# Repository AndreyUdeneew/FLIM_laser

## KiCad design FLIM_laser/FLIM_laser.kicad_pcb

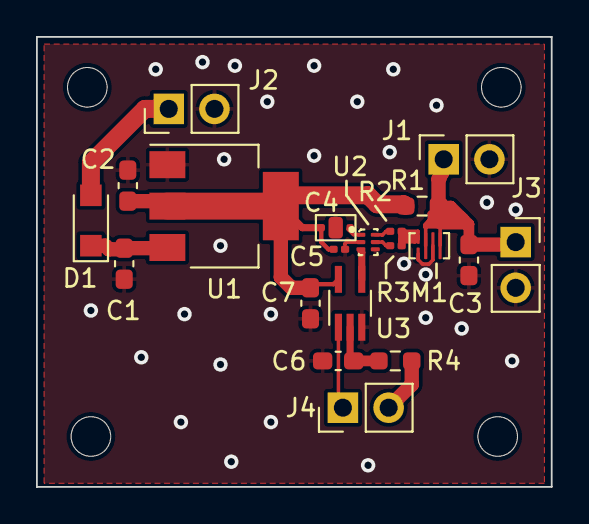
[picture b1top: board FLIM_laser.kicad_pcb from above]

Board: 2 copper layers, 28.6 x 25.0 mm, 20 parts (0 on the bottom side), 13 nets.

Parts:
C1, C2, C3, C6, C7: C; C_0603_1608Metric_Pad1.08x0.95mm_HandSolder
C4: C_Feedthrough; YFF18PW0J474M
C5: C; C_0201_0603Metric
D1: PMEG40T10ER; Nexperia_CFP3_SOD-123W
J1, J3: Conn_01x02_Male; PinSocket_1x02_P2.54mm_Vertical
J2, J4: Conn_01x02_Male; PinHeader_1x02_P2.54mm_Vertical
M1: EP2014C; EPC2014C
R1, R4: R; R_0603_1608Metric_Pad0.98x0.95mm_HandSolder
R2, R3: R; R_0201_0603Metric
U1: AMS1117-5.0; SOT-223-3_TabPin2
U2: LMG1020
U3: 74LVC1G08; SOT-353_SC-70-5_Handsoldering

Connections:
+5V: C2.1, C4.1, C5.1, C7.1, R1.1, U1.2 (VO), U3.5 (VCC)
GND: C1.2, C2.2, C3.2, C4.2, C5.2, C6.2, C7.2, J1.2, J2.2, J3.2, M1.2 (Sub), M1.4 (S), U1.1 (GND), U2.B1 (GND), U2.C2 (IN-), U3.3 (GND)
unnamed: C1.1, D1.1 (K), U1.3 (VI)
unnamed: C3.1, J1.1, J3.1, M1.3 (D), M1.5 (D), R1.2
unnamed: C6.1, R4.2, U3.2
unnamed: D1.2 (A), J2.1
unnamed: J4.1, U3.1
unnamed: J4.2, R4.1
unnamed: M1.1 (G), R2.2, R3.2
unnamed: R2.1, U2.A2 (OUTH)
unnamed: R3.1, U2.B2 (OUTL)
unnamed: C4.3, U2.A1 (VDD)
unnamed: U2.C1 (IN+), U3.4

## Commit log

2022-03-09 v0.1 files were created
2022-03-10 v0.1 library and circuit were created
2022-03-10 v0.2 correct connector was added
2022-03-10 v0.3 circuit is ready
2022-05-06 v0.4 correct symbols were added
2022-05-07 v0.5 power source was added
2022-05-07 v0.6 input shottky was added
2022-05-10 v0.7 PCB prototype was created, components were decomposed
2022-05-12 v0.8 footprints were corrected
2022-05-12 v0.9 decomposition was completed
2022-05-12 v0.91 some changes
2022-05-12 v0.92 subcompleted
2022-05-12 v0.93 subcomplected 2
2022-05-13 v0.94 something
2022-05-14 v0.95 DRC was conducted
2022-05-16 v0.96 Silk was corrected
2022-05-16 v0.97 Silk was corrected
2022-05-16 v0.98 Gerbers and drl were created
